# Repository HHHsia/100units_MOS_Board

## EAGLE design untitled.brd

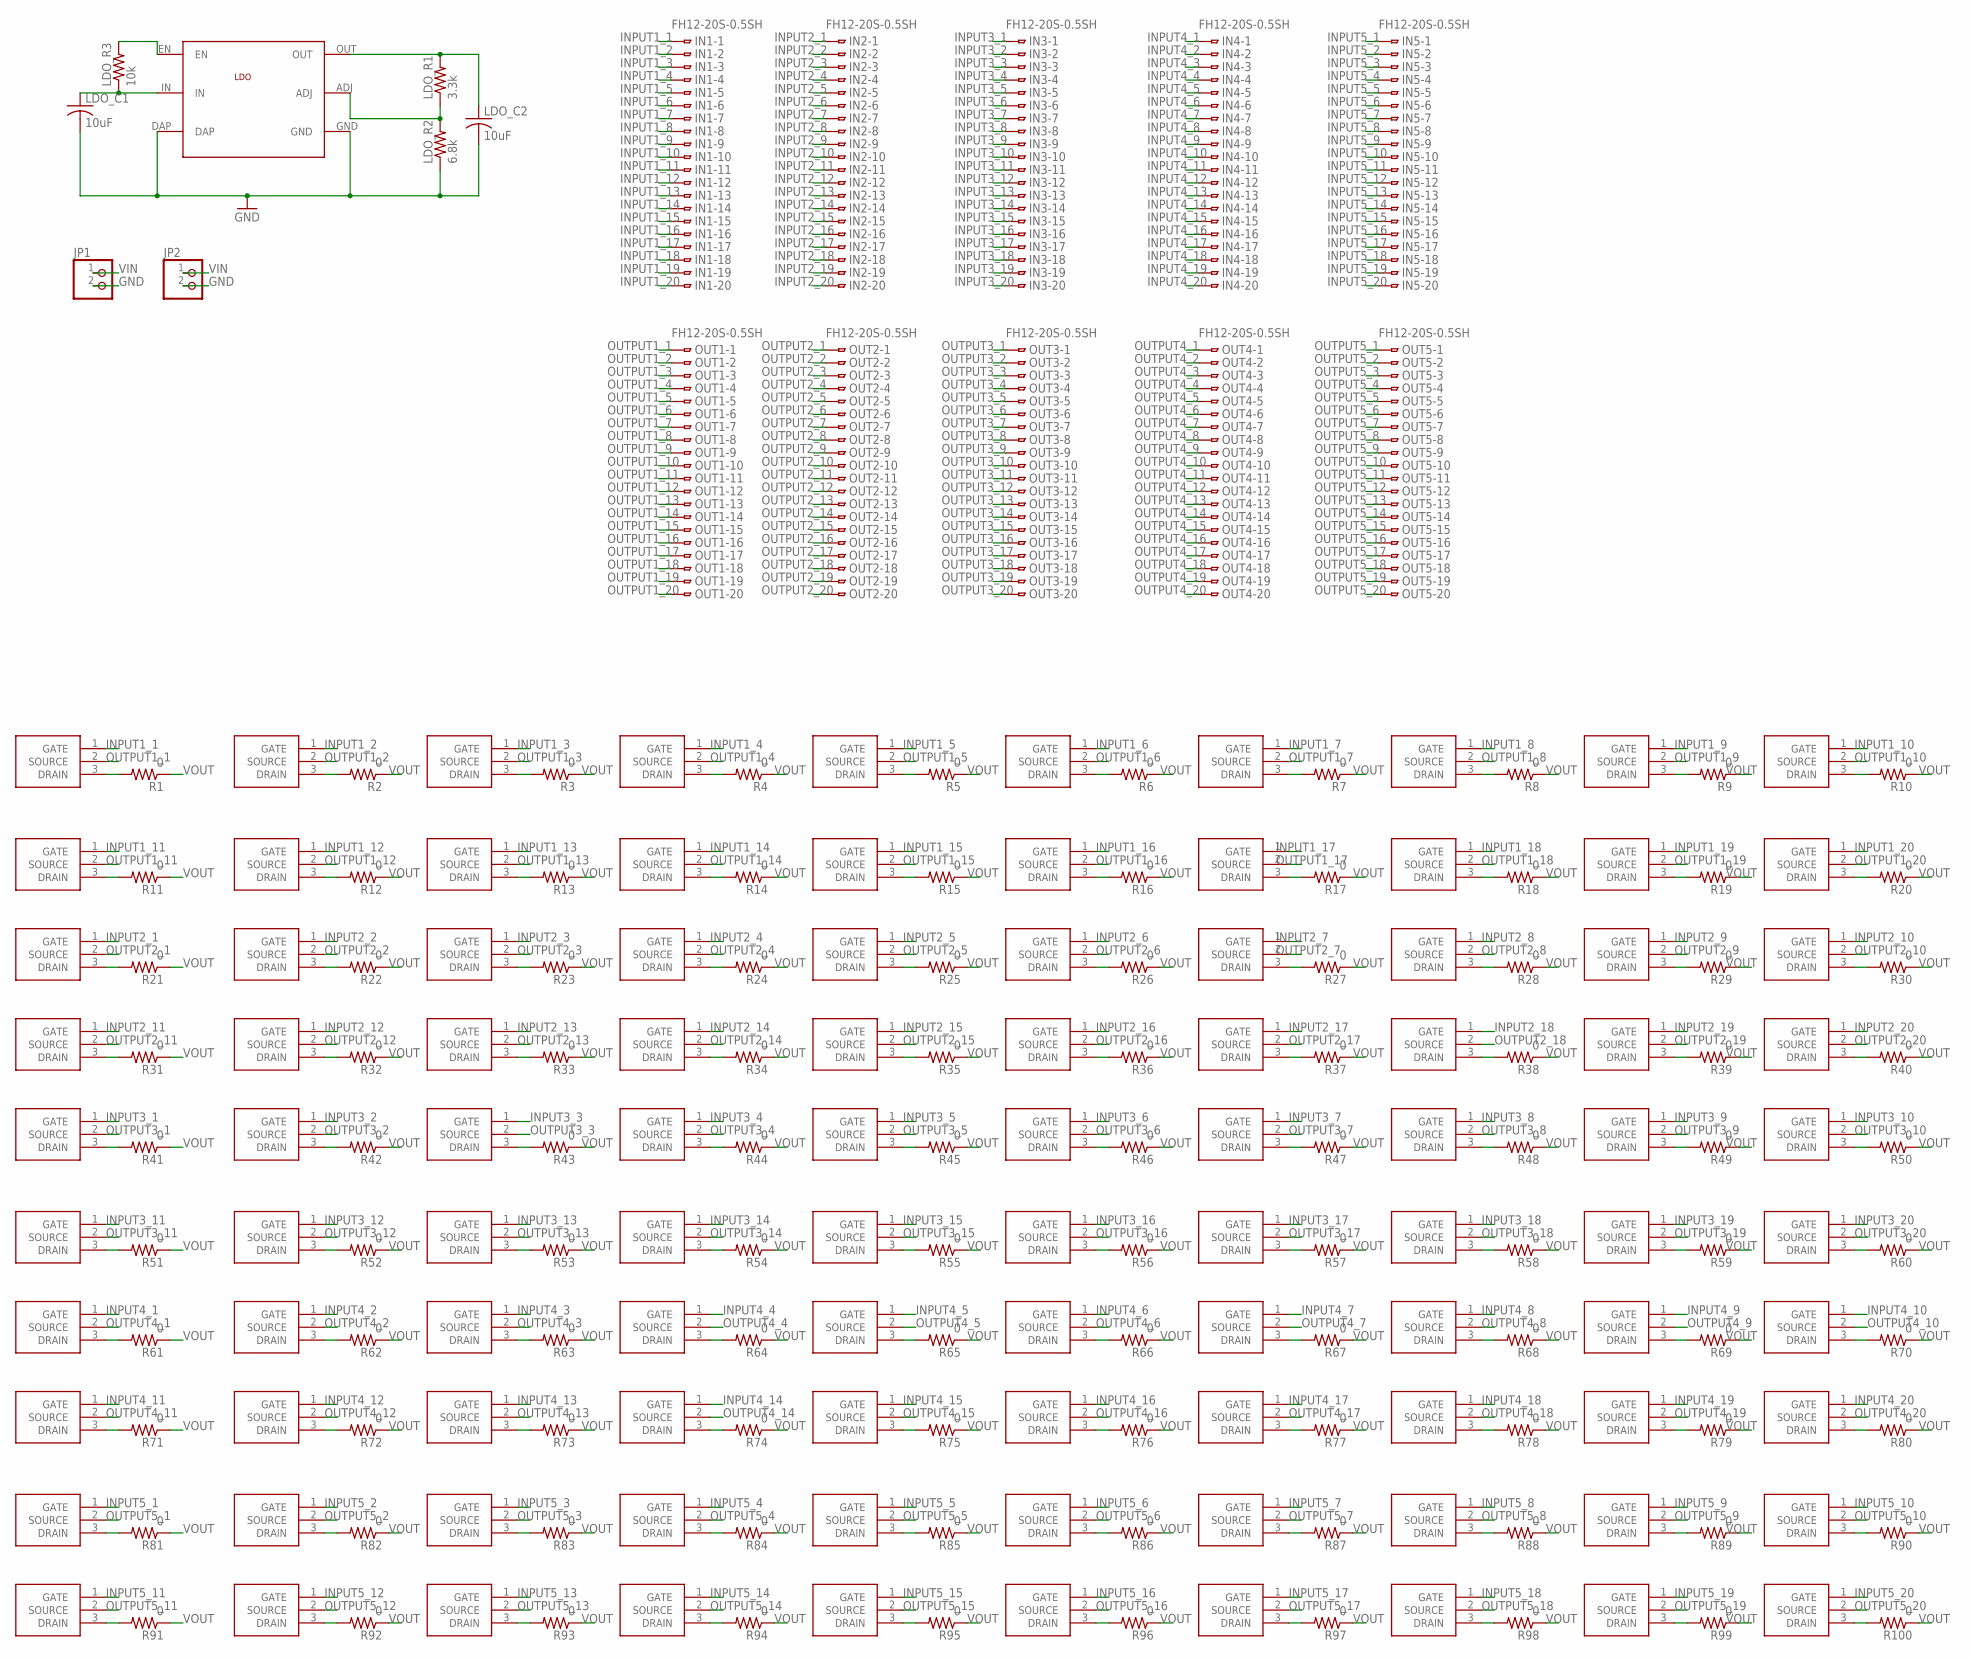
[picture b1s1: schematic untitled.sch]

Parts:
IN1, IN2, IN3, IN4, IN5: FH12-20S-0.5SH
JP1, JP2: PINHD-1X2; 1X02
LDO: LP38501TS_ADJ
LDO_C1, LDO_C2: 10uF; C0805
LDO_R1: 3.3k; R0805
LDO_R2: 6.8k; R0805
LDO_R3: 10k; R0805
MOS1, MOS2, MOS3, MOS4, MOS5, MOS6, MOS7, MOS8, MOS9, MOS10, MOS11, MOS12, MOS13, MOS14, MOS15, MOS16, MOS17, MOS18, MOS19, MOS20, MOS21, MOS22, MOS23, MOS24, MOS25, MOS26, MOS27, MOS28, MOS29, MOS30, MOS31, MOS32, MOS33, MOS34, MOS35, MOS36, MOS37, MOS38, MOS39, MOS40, MOS41, MOS42, MOS43, MOS44, MOS45, MOS46, MOS47, MOS48, MOS49, MOS50, MOS51, MOS52, MOS53, MOS54, MOS55, MOS56, MOS57, MOS58, MOS59, MOS60, MOS61, MOS62, MOS63, MOS64, MOS65, MOS66, MOS67, MOS68, MOS69, MOS70, MOS71, MOS72, MOS73, MOS74, MOS75, MOS76, MOS77, MOS78, MOS79, MOS80, MOS81, MOS82, MOS83, MOS84, MOS85, MOS86, MOS87, MOS88, MOS89, MOS90, MOS91, MOS92, MOS93, MOS94, MOS95, MOS96, MOS97, MOS98, MOS99, MOS100: NX6008NBKNX6008NBK; SOT95P240X110-3N
OUT1, OUT2, OUT3, OUT4, OUT5: FH12-20S-0.5SH
R1, R2, R3, R4, R5, R6, R7, R8, R9, R10, R11, R12, R13, R14, R15, R16, R17, R18, R19, R20, R21, R22, R23, R24, R25, R26, R27, R28, R29, R30, R31, R32, R33, R34, R35, R36, R37, R38, R39, R40, R41, R42, R43, R44, R45, R46, R47, R48, R49, R50, R51, R52, R53, R54, R55, R56, R57, R58, R59, R60, R61, R62, R63, R64, R65, R66, R67, R68, R69, R70, R71, R72, R73, R74, R75, R76, R77, R78, R79, R80, R81, R82, R83, R84, R85, R86, R87, R88, R89, R90, R91, R92, R93, R94, R95, R96, R97, R98, R99, R100: 0; R0805

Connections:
GND: JP1.2, JP2.2, LDO.DAP, LDO.GND, LDO_C1.2, LDO_C2.2, LDO_R2.1
INPUT1_1: IN1.1, MOS1.1 (GATE)
INPUT1_2: IN1.2, MOS2.1 (GATE)
INPUT1_3: IN1.3, MOS3.1 (GATE)
INPUT1_4: IN1.4, MOS4.1 (GATE)
INPUT1_5: IN1.5, MOS5.1 (GATE)
INPUT1_6: IN1.6, MOS6.1 (GATE)
INPUT1_7: IN1.7, MOS7.1 (GATE)
INPUT1_8: IN1.8, MOS8.1 (GATE)
INPUT1_9: IN1.9, MOS9.1 (GATE)
INPUT1_10: IN1.10, MOS10.1 (GATE)
INPUT1_11: IN1.11, MOS11.1 (GATE)
INPUT1_12: IN1.12, MOS12.1 (GATE)
INPUT1_13: IN1.13, MOS13.1 (GATE)
INPUT1_14: IN1.14, MOS14.1 (GATE)
INPUT1_15: IN1.15, MOS15.1 (GATE)
INPUT1_16: IN1.16, MOS16.1 (GATE)
INPUT1_17: IN1.17, MOS17.1 (GATE)
INPUT1_18: IN1.18, MOS18.1 (GATE)
INPUT1_19: IN1.19, MOS19.1 (GATE)
INPUT1_20: IN1.20, MOS20.1 (GATE)
INPUT2_1: IN2.1, MOS21.1 (GATE)
INPUT2_2: IN2.2, MOS22.1 (GATE)
INPUT2_3: IN2.3, MOS23.1 (GATE)
INPUT2_4: IN2.4, MOS24.1 (GATE)
INPUT2_5: IN2.5, MOS25.1 (GATE)
INPUT2_6: IN2.6, MOS26.1 (GATE)
INPUT2_7: IN2.7, MOS27.1 (GATE)
INPUT2_8: IN2.8, MOS28.1 (GATE)
INPUT2_9: IN2.9, MOS29.1 (GATE)
INPUT2_10: IN2.10, MOS30.1 (GATE)
INPUT2_11: IN2.11, MOS31.1 (GATE)
INPUT2_12: IN2.12, MOS32.1 (GATE)
INPUT2_13: IN2.13, MOS33.1 (GATE)
INPUT2_14: IN2.14, MOS34.1 (GATE)
INPUT2_15: IN2.15, MOS35.1 (GATE)
INPUT2_16: IN2.16, MOS36.1 (GATE)
INPUT2_17: IN2.17, MOS37.1 (GATE)
INPUT2_18: IN2.18, MOS38.1 (GATE)
INPUT2_19: IN2.19, MOS39.1 (GATE)
INPUT2_20: IN2.20, MOS40.1 (GATE)
INPUT3_1: IN3.1, MOS41.1 (GATE)
INPUT3_2: IN3.2, MOS42.1 (GATE)
INPUT3_3: IN3.3, MOS43.1 (GATE)
INPUT3_4: IN3.4, MOS44.1 (GATE)
INPUT3_5: IN3.5, MOS45.1 (GATE)
INPUT3_6: IN3.6, MOS46.1 (GATE)
INPUT3_7: IN3.7, MOS47.1 (GATE)
INPUT3_8: IN3.8, MOS48.1 (GATE)
INPUT3_9: IN3.9, MOS49.1 (GATE)
INPUT3_10: IN3.10, MOS50.1 (GATE)
INPUT3_11: IN3.11, MOS51.1 (GATE)
INPUT3_12: IN3.12, MOS52.1 (GATE)
INPUT3_13: IN3.13, MOS53.1 (GATE)
INPUT3_14: IN3.14, MOS54.1 (GATE)
INPUT3_15: IN3.15, MOS55.1 (GATE)
INPUT3_16: IN3.16, MOS56.1 (GATE)
INPUT3_17: IN3.17, MOS57.1 (GATE)
INPUT3_18: IN3.18, MOS58.1 (GATE)
INPUT3_19: IN3.19, MOS59.1 (GATE)
INPUT3_20: IN3.20, MOS60.1 (GATE)
INPUT4_1: IN4.1, MOS61.1 (GATE)
INPUT4_2: IN4.2, MOS62.1 (GATE)
INPUT4_3: IN4.3, MOS63.1 (GATE)
INPUT4_4: IN4.4, MOS64.1 (GATE)
INPUT4_5: IN4.5, MOS65.1 (GATE)
INPUT4_6: IN4.6, MOS66.1 (GATE)
INPUT4_7: IN4.7, MOS67.1 (GATE)
INPUT4_8: IN4.8, MOS68.1 (GATE)
INPUT4_9: IN4.9, MOS69.1 (GATE)
INPUT4_10: IN4.10, MOS70.1 (GATE)
INPUT4_11: IN4.11, MOS71.1 (GATE)
INPUT4_12: IN4.12, MOS72.1 (GATE)
INPUT4_13: IN4.13, MOS73.1 (GATE)
INPUT4_14: IN4.14, MOS74.1 (GATE)
INPUT4_15: IN4.15, MOS75.1 (GATE)
INPUT4_16: IN4.16, MOS76.1 (GATE)
INPUT4_17: IN4.17, MOS77.1 (GATE)
INPUT4_18: IN4.18, MOS78.1 (GATE)
INPUT4_19: IN4.19, MOS79.1 (GATE)
INPUT4_20: IN4.20, MOS80.1 (GATE)
INPUT5_1: IN5.1, MOS81.1 (GATE)
INPUT5_2: IN5.2, MOS82.1 (GATE)
INPUT5_3: IN5.3, MOS83.1 (GATE)
INPUT5_4: IN5.4, MOS84.1 (GATE)
INPUT5_5: IN5.5, MOS85.1 (GATE)
INPUT5_6: IN5.6, MOS86.1 (GATE)
INPUT5_7: IN5.7, MOS87.1 (GATE)
INPUT5_8: IN5.8, MOS88.1 (GATE)
INPUT5_9: IN5.9, MOS89.1 (GATE)
INPUT5_10: IN5.10, MOS90.1 (GATE)
INPUT5_11: IN5.11, MOS91.1 (GATE)
INPUT5_12: IN5.12, MOS92.1 (GATE)
INPUT5_13: IN5.13, MOS93.1 (GATE)
INPUT5_14: IN5.14, MOS94.1 (GATE)
INPUT5_15: IN5.15, MOS95.1 (GATE)
INPUT5_16: IN5.16, MOS96.1 (GATE)
INPUT5_17: IN5.17, MOS97.1 (GATE)
INPUT5_18: IN5.18, MOS98.1 (GATE)
INPUT5_19: IN5.19, MOS99.1 (GATE)
INPUT5_20: IN5.20, MOS100.1 (GATE)
unnamed: LDO.EN, LDO_R3.2
unnamed: MOS77.3 (DRAIN), R77.2
unnamed: MOS81.3 (DRAIN), R81.2
unnamed: LDO.ADJ, LDO_R1.1, LDO_R2.2
unnamed: MOS1.3 (DRAIN), R1.2
unnamed: MOS2.3 (DRAIN), R2.2
unnamed: MOS82.3 (DRAIN), R82.2
unnamed: MOS83.3 (DRAIN), R83.2
unnamed: MOS84.3 (DRAIN), R84.2
unnamed: MOS3.3 (DRAIN), R3.2
unnamed: MOS85.3 (DRAIN), R85.2
unnamed: MOS86.3 (DRAIN), R86.2
unnamed: MOS87.3 (DRAIN), R87.2
unnamed: MOS4.3 (DRAIN), R4.2
unnamed: MOS88.3 (DRAIN), R88.2
unnamed: MOS89.3 (DRAIN), R89.2
unnamed: MOS90.3 (DRAIN), R90.2
unnamed: MOS5.3 (DRAIN), R5.2
unnamed: MOS91.3 (DRAIN), R91.2
unnamed: MOS92.3 (DRAIN), R92.2
unnamed: MOS93.3 (DRAIN), R93.2
unnamed: MOS6.3 (DRAIN), R6.2
unnamed: MOS94.3 (DRAIN), R94.2
unnamed: MOS95.3 (DRAIN), R95.2
unnamed: MOS96.3 (DRAIN), R96.2
unnamed: MOS7.3 (DRAIN), R7.2
unnamed: MOS98.3 (DRAIN), R98.2
unnamed: MOS99.3 (DRAIN), R99.2
unnamed: MOS100.3 (DRAIN), R100.2
unnamed: MOS8.3 (DRAIN), R8.2
unnamed: MOS97.3 (DRAIN), R97.2
unnamed: MOS9.3 (DRAIN), R9.2
unnamed: MOS10.3 (DRAIN), R10.2
unnamed: MOS11.3 (DRAIN), R11.2
unnamed: MOS12.3 (DRAIN), R12.2
unnamed: MOS13.3 (DRAIN), R13.2
unnamed: MOS14.3 (DRAIN), R14.2
unnamed: MOS15.3 (DRAIN), R15.2
unnamed: MOS16.3 (DRAIN), R16.2
unnamed: MOS17.3 (DRAIN), R17.2
unnamed: MOS18.3 (DRAIN), R18.2
unnamed: MOS19.3 (DRAIN), R19.2
unnamed: MOS20.3 (DRAIN), R20.2
unnamed: MOS21.3 (DRAIN), R21.2
unnamed: MOS22.3 (DRAIN), R22.2
unnamed: MOS23.3 (DRAIN), R23.2
unnamed: MOS24.3 (DRAIN), R24.2
unnamed: MOS25.3 (DRAIN), R25.2
unnamed: MOS26.3 (DRAIN), R26.2
unnamed: MOS27.3 (DRAIN), R27.2
unnamed: MOS28.3 (DRAIN), R28.2
unnamed: MOS29.3 (DRAIN), R29.2
unnamed: MOS30.3 (DRAIN), R30.2
unnamed: MOS31.3 (DRAIN), R31.2
unnamed: MOS32.3 (DRAIN), R32.2
unnamed: MOS33.3 (DRAIN), R33.2
unnamed: MOS34.3 (DRAIN), R34.2
unnamed: MOS35.3 (DRAIN), R35.2
unnamed: MOS36.3 (DRAIN), R36.2
unnamed: MOS37.3 (DRAIN), R37.2
unnamed: MOS38.3 (DRAIN), R38.2
unnamed: MOS39.3 (DRAIN), R39.2
unnamed: MOS40.3 (DRAIN), R40.2
unnamed: MOS41.3 (DRAIN), R41.2
unnamed: MOS42.3 (DRAIN), R42.2
unnamed: MOS43.3 (DRAIN), R43.2
unnamed: MOS44.3 (DRAIN), R44.2
unnamed: MOS45.3 (DRAIN), R45.2
unnamed: MOS46.3 (DRAIN), R46.2
unnamed: MOS47.3 (DRAIN), R47.2
unnamed: MOS48.3 (DRAIN), R48.2
unnamed: MOS49.3 (DRAIN), R49.2
unnamed: MOS50.3 (DRAIN), R50.2
unnamed: MOS51.3 (DRAIN), R51.2
unnamed: MOS52.3 (DRAIN), R52.2
unnamed: MOS53.3 (DRAIN), R53.2
unnamed: MOS54.3 (DRAIN), R54.2
unnamed: MOS55.3 (DRAIN), R55.2
unnamed: MOS56.3 (DRAIN), R56.2
unnamed: MOS57.3 (DRAIN), R57.2
unnamed: MOS58.3 (DRAIN), R58.2
unnamed: MOS59.3 (DRAIN), R59.2
unnamed: MOS60.3 (DRAIN), R60.2
unnamed: MOS61.3 (DRAIN), R61.2
unnamed: MOS62.3 (DRAIN), R62.2
unnamed: MOS63.3 (DRAIN), R63.2
unnamed: MOS64.3 (DRAIN), R64.2
unnamed: MOS65.3 (DRAIN), R65.2
unnamed: MOS66.3 (DRAIN), R66.2
unnamed: MOS67.3 (DRAIN), R67.2
unnamed: MOS68.3 (DRAIN), R68.2
unnamed: MOS69.3 (DRAIN), R69.2
unnamed: MOS70.3 (DRAIN), R70.2
unnamed: MOS71.3 (DRAIN), R71.2
unnamed: MOS72.3 (DRAIN), R72.2
unnamed: MOS73.3 (DRAIN), R73.2
unnamed: MOS74.3 (DRAIN), R74.2
unnamed: MOS75.3 (DRAIN), R75.2
unnamed: MOS76.3 (DRAIN), R76.2
unnamed: MOS78.3 (DRAIN), R78.2
unnamed: MOS79.3 (DRAIN), R79.2
unnamed: MOS80.3 (DRAIN), R80.2
OUTPUT1_1: MOS1.2 (SOURCE), OUT1.1
OUTPUT1_2: MOS2.2 (SOURCE), OUT1.2
OUTPUT1_3: MOS3.2 (SOURCE), OUT1.3
OUTPUT1_4: MOS4.2 (SOURCE), OUT1.4
OUTPUT1_5: MOS5.2 (SOURCE), OUT1.5
OUTPUT1_6: MOS6.2 (SOURCE), OUT1.6
OUTPUT1_7: MOS7.2 (SOURCE), OUT1.7
OUTPUT1_8: MOS8.2 (SOURCE), OUT1.8
OUTPUT1_9: MOS9.2 (SOURCE), OUT1.9
OUTPUT1_10: MOS10.2 (SOURCE), OUT1.10
OUTPUT1_11: MOS11.2 (SOURCE), OUT1.11
OUTPUT1_12: MOS12.2 (SOURCE), OUT1.12
OUTPUT1_13: MOS13.2 (SOURCE), OUT1.13
OUTPUT1_14: MOS14.2 (SOURCE), OUT1.14
OUTPUT1_15: MOS15.2 (SOURCE), OUT1.15
OUTPUT1_16: MOS16.2 (SOURCE), OUT1.16
OUTPUT1_17: MOS17.2 (SOURCE), OUT1.17
OUTPUT1_18: MOS18.2 (SOURCE), OUT1.18
OUTPUT1_19: MOS19.2 (SOURCE), OUT1.19
OUTPUT1_20: MOS20.2 (SOURCE), OUT1.20
OUTPUT2_1: MOS21.2 (SOURCE), OUT2.1
OUTPUT2_2: MOS22.2 (SOURCE), OUT2.2
OUTPUT2_3: MOS23.2 (SOURCE), OUT2.3
OUTPUT2_4: MOS24.2 (SOURCE), OUT2.4
OUTPUT2_5: MOS25.2 (SOURCE), OUT2.5
OUTPUT2_6: MOS26.2 (SOURCE), OUT2.6
OUTPUT2_7: MOS27.2 (SOURCE), OUT2.7
OUTPUT2_8: MOS28.2 (SOURCE), OUT2.8
OUTPUT2_9: MOS29.2 (SOURCE), OUT2.9
OUTPUT2_10: MOS30.2 (SOURCE), OUT2.10
OUTPUT2_11: MOS31.2 (SOURCE), OUT2.11
OUTPUT2_12: MOS32.2 (SOURCE), OUT2.12
OUTPUT2_13: MOS33.2 (SOURCE), OUT2.13
OUTPUT2_14: MOS34.2 (SOURCE), OUT2.14
OUTPUT2_15: MOS35.2 (SOURCE), OUT2.15
OUTPUT2_16: MOS36.2 (SOURCE), OUT2.16
OUTPUT2_17: MOS37.2 (SOURCE), OUT2.17
OUTPUT2_18: MOS38.2 (SOURCE), OUT2.18
OUTPUT2_19: MOS39.2 (SOURCE), OUT2.19
OUTPUT2_20: MOS40.2 (SOURCE), OUT2.20
OUTPUT3_1: MOS41.2 (SOURCE), OUT3.1
OUTPUT3_2: MOS42.2 (SOURCE), OUT3.2
OUTPUT3_3: MOS43.2 (SOURCE), OUT3.3
OUTPUT3_4: MOS44.2 (SOURCE), OUT3.4
OUTPUT3_5: MOS45.2 (SOURCE), OUT3.5
OUTPUT3_6: MOS46.2 (SOURCE), OUT3.6
OUTPUT3_7: MOS47.2 (SOURCE), OUT3.7
OUTPUT3_8: MOS48.2 (SOURCE), OUT3.8
OUTPUT3_9: MOS49.2 (SOURCE), OUT3.9
OUTPUT3_10: MOS50.2 (SOURCE), OUT3.10
OUTPUT3_11: MOS51.2 (SOURCE), OUT3.11
OUTPUT3_12: MOS52.2 (SOURCE), OUT3.12
OUTPUT3_13: MOS53.2 (SOURCE), OUT3.13
OUTPUT3_14: MOS54.2 (SOURCE), OUT3.14
OUTPUT3_15: MOS55.2 (SOURCE), OUT3.15
OUTPUT3_16: MOS56.2 (SOURCE), OUT3.16
OUTPUT3_17: MOS57.2 (SOURCE), OUT3.17
OUTPUT3_18: MOS58.2 (SOURCE), OUT3.18
OUTPUT3_19: MOS59.2 (SOURCE), OUT3.19
OUTPUT3_20: MOS60.2 (SOURCE), OUT3.20
OUTPUT4_1: MOS61.2 (SOURCE), OUT4.1
OUTPUT4_2: MOS62.2 (SOURCE), OUT4.2
OUTPUT4_3: MOS63.2 (SOURCE), OUT4.3
OUTPUT4_4: MOS64.2 (SOURCE), OUT4.4
OUTPUT4_5: MOS65.2 (SOURCE), OUT4.5
OUTPUT4_6: MOS66.2 (SOURCE), OUT4.6
OUTPUT4_7: MOS67.2 (SOURCE), OUT4.7
OUTPUT4_8: MOS68.2 (SOURCE), OUT4.8
OUTPUT4_9: MOS69.2 (SOURCE), OUT4.9
OUTPUT4_10: MOS70.2 (SOURCE), OUT4.10
OUTPUT4_11: MOS71.2 (SOURCE), OUT4.11
OUTPUT4_12: MOS72.2 (SOURCE), OUT4.12
OUTPUT4_13: MOS73.2 (SOURCE), OUT4.13
OUTPUT4_14: MOS74.2 (SOURCE), OUT4.14
OUTPUT4_15: MOS75.2 (SOURCE), OUT4.15
OUTPUT4_16: MOS76.2 (SOURCE), OUT4.16
OUTPUT4_17: MOS77.2 (SOURCE), OUT4.17
OUTPUT4_18: MOS78.2 (SOURCE), OUT4.18
OUTPUT4_19: MOS79.2 (SOURCE), OUT4.19
OUTPUT4_20: MOS80.2 (SOURCE), OUT4.20
OUTPUT5_1: MOS81.2 (SOURCE), OUT5.1
OUTPUT5_2: MOS82.2 (SOURCE), OUT5.2
OUTPUT5_3: MOS83.2 (SOURCE), OUT5.3
OUTPUT5_4: MOS84.2 (SOURCE), OUT5.4
OUTPUT5_5: MOS85.2 (SOURCE), OUT5.5
OUTPUT5_6: MOS86.2 (SOURCE), OUT5.6
OUTPUT5_7: MOS87.2 (SOURCE), OUT5.7
OUTPUT5_8: MOS88.2 (SOURCE), OUT5.8
OUTPUT5_9: MOS89.2 (SOURCE), OUT5.9
OUTPUT5_10: MOS90.2 (SOURCE), OUT5.10
OUTPUT5_11: MOS91.2 (SOURCE), OUT5.11
OUTPUT5_12: MOS92.2 (SOURCE), OUT5.12
OUTPUT5_13: MOS93.2 (SOURCE), OUT5.13
OUTPUT5_14: MOS94.2 (SOURCE), OUT5.14
OUTPUT5_15: MOS95.2 (SOURCE), OUT5.15
OUTPUT5_16: MOS96.2 (SOURCE), OUT5.16
OUTPUT5_17: MOS97.2 (SOURCE), OUT5.17
OUTPUT5_18: MOS98.2 (SOURCE), OUT5.18
OUTPUT5_19: MOS99.2 (SOURCE), OUT5.19
OUTPUT5_20: MOS100.2 (SOURCE), OUT5.20
VIN: JP1.1, JP2.1, LDO.IN, LDO_C1.1, LDO_R3.1
VOUT: LDO.OUT, LDO_C2.1, LDO_R1.2, R1.1, R2.1, R3.1, R4.1, R5.1, R6.1, R7.1, R8.1, R9.1, R10.1, R11.1, R12.1, R13.1, R14.1, R15.1, R16.1, R17.1, R18.1, R19.1, R20.1, R21.1, R22.1, R23.1, R24.1, R25.1, R26.1, R27.1, R28.1, R29.1, R30.1, R31.1, R32.1, R33.1, R34.1, R35.1, R36.1, R37.1, R38.1, R39.1, R40.1, R41.1, R42.1, R43.1, R44.1, R45.1, R46.1, R47.1, R48.1, R49.1, R50.1, R51.1, R52.1, R53.1, R54.1, R55.1, R56.1, R57.1, R58.1, R59.1, R60.1, R61.1, R62.1, R63.1, R64.1, R65.1, R66.1, R67.1, R68.1, R69.1, R70.1, R71.1, R72.1, R73.1, R74.1, R75.1, R76.1, R77.1, R78.1, R79.1, R80.1, R81.1, R82.1, R83.1, R84.1, R85.1, R86.1, R87.1, R88.1, R89.1, R90.1, R91.1, R92.1, R93.1, R94.1, R95.1, R96.1, R97.1, R98.1, R99.1, R100.1

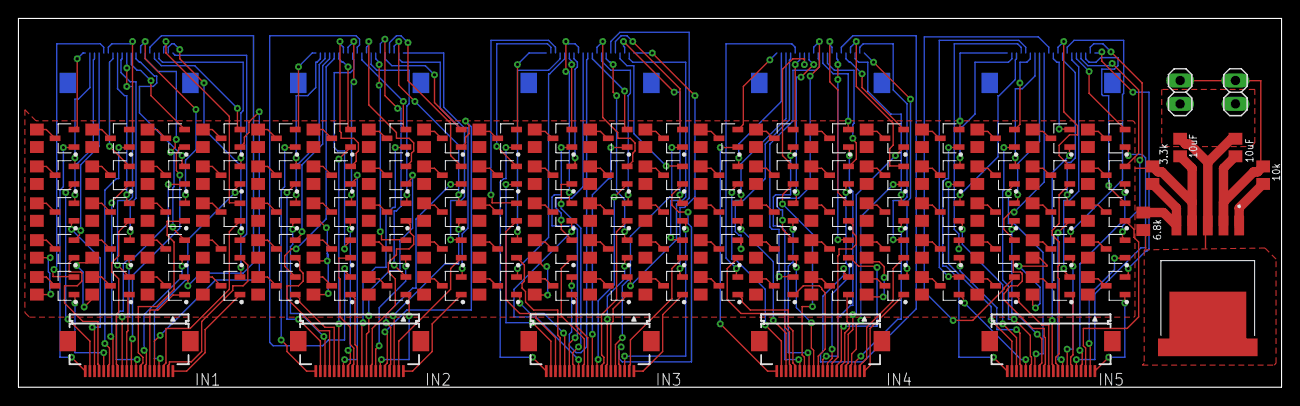
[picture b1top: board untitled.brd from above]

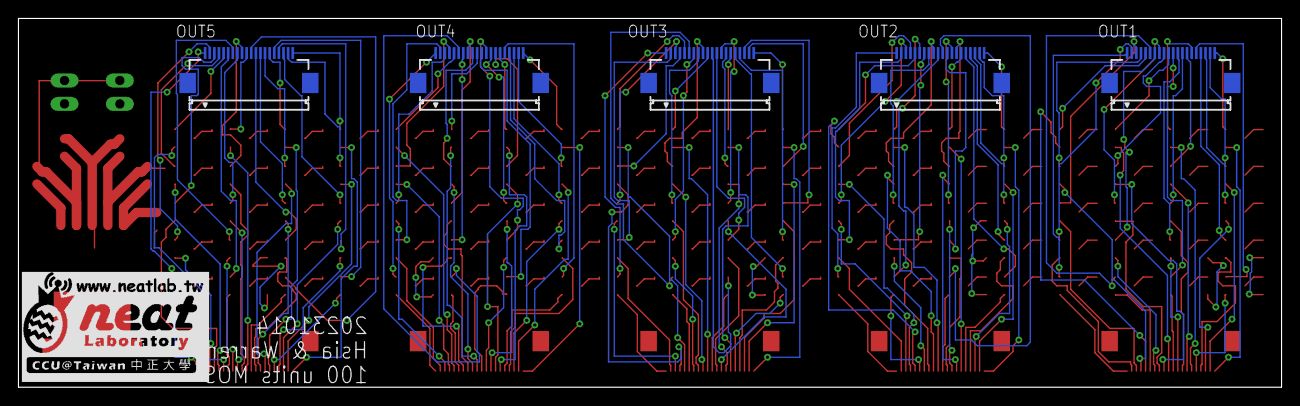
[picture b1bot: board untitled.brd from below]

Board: 2 copper layers, 137.0 x 40.0 mm, 219 parts (6 on the bottom side), 305 nets.

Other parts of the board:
U$1: LOGO_SCALE_2.0

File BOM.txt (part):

Partlist exported from C:/Users/PW0000/Downloads/100units_MOS_Board/untitled.sch at 2023/10/20 下午 04:18

Part   Value              Device             Package          Description                        MF MPN                OC_FARNELL OC_NEWARK POPULARITY SPICEPREFIX
IN1    FH12-20S-0.5SH     FH12-20S-0.5SH     FH12-20S-0.5SH   0.5mm Pitch Connectors For FPC/FFC    FH12-20S-0.5SH(55) 1324549    34M6166   0                     
IN2    FH12-20S-0.5SH     FH12-20S-0.5SH     FH12-20S-0.5SH   0.5mm Pitch Connectors For FPC/FFC    FH12-20S-0.5SH(55) 1324549    34M6166   0                     
IN3    FH12-20S-0.5SH     FH12-20S-0.5SH     FH12-20S-0.5SH   0.5mm Pitch Connectors For FPC/FFC    FH12-20S-0.5SH(55) 1324549    34M6166   0                     
IN4    FH12-20S-0.5SH     FH12-20S-0.5SH     FH12-20S-0.5SH   0.5mm Pitch Connectors For FPC/FFC    FH12-20S-0.5SH(55) 1324549    34M6166   0                     
IN5    FH12-20S-0.5SH     FH12-20S-0.5SH     FH12-20S-0.5SH   0.5mm Pitch Connectors For FPC/FFC    FH12-20S-0.5SH(55) 1324549    34M6166   0                     
JP1                       PINHD-1X2          1X02             PIN HEADER                                                                    98                    
JP2                       PINHD-1X2          1X02             PIN HEADER                                                                    98                    
LDO                       LP38501TS_ADJ      LP38501TS_ADJ                                                                                                        
LDO_C1 10uF               C-USC0805          C0805            CAPACITOR, American symbol                                                    63         C          
LDO_C2 10uF               C-USC0805          C0805            CAPACITOR, American symbol                                                    63         C          
LDO_R1 3.3k               R-US_R0805         R0805            RESISTOR, American symbol                                                     85         R          
LDO_R2 6.8k               R-US_R0805         R0805            RESISTOR, American symbol                                                     85         R          
LDO_R3 10k                R-US_R0805         R0805            RESISTOR, American symbol                                                     85         R          
MOS1   NX6008NBKNX6008NBK NX6008NBKNX6008NBK SOT95P240X110-3N                                                                                                     
MOS2   NX6008NBKNX6008NBK NX6008NBKNX6008NBK SOT95P240X110-3N                                                                                                     
MOS3   NX6008NBKNX6008NBK NX6008NBKNX6008NBK SOT95P240X110-3N                                                                                                     
MOS4   NX6008NBKNX6008NBK NX6008NBKNX6008NBK SOT95P240X110-3N                                                                                                     
MOS5   NX6008NBKNX6008NBK NX6008NBKNX6008NBK SOT95P240X110-3N                                                                                                     
MOS6   NX6008NBKNX6008NBK NX6008NBKNX6008NBK SOT95P240X110-3N                                                                                                     
MOS7   NX6008NBKNX6008NBK NX6008NBKNX6008NBK SOT95P240X110-3N                                                                                                     
MOS8   NX6008NBKNX6008NBK NX6008NBKNX6008NBK SOT95P240X110-3N                                                                                                     
MOS9   NX6008NBKNX6008NBK NX6008NBKNX6008NBK SOT95P240X110-3N                                                                                                     
MOS10  NX6008NBKNX6008NBK NX6008NBKNX6008NBK SOT95P240X110-3N                                                                                                     
MOS11  NX6008NBKNX6008NBK NX6008NBKNX6008NBK SOT95P240X110-3N                                                                                                     
MOS12  NX6008NBKNX6008NBK NX6008NBKNX6008NBK SOT95P240X110-3N                                                                                                     
MOS13  NX6008NBKNX6008NBK NX6008NBKNX6008NBK SOT95P240X110-3N                                                                                                     
MOS14  NX6008NBKNX6008NBK NX6008NBKNX6008NBK SOT95P240X110-3N                                                                                                     
MOS15  NX6008NBKNX6008NBK NX6008NBKNX6008NBK SOT95P240X110-3N                                                                                                     
MOS16  NX6008NBKNX6008NBK NX6008NBKNX6008NBK SOT95P240X110-3N                                                                                                     
MOS17  NX6008NBKNX6008NBK NX6008NBKNX6008NBK SOT95P240X110-3N                                                                                                     
MOS18  NX6008NBKNX6008NBK NX6008NBKNX6008NBK SOT95P240X110-3N                                                                                                     
MOS19  NX6008NBKNX6008NBK NX6008NBKNX6008NBK SOT95P240X110-3N                                                                                                     
MOS20  NX6008NBKNX6008NBK NX6008NBKNX6008NBK SOT95P240X110-3N                                                                                                     
MOS21  NX6008NBKNX6008NBK NX6008NBKNX6008NBK SOT95P240X110-3N                                                                                                     
MOS22  NX6008NBKNX6008NBK NX6008NBKNX6008NBK SOT95P240X110-3N                                                                                                     
MOS23  NX6008NBKNX6008NBK NX6008NBKNX6008NBK SOT95P240X110-3N                                                                                                     
MOS24  NX6008NBKNX6008NBK NX6008NBKNX6008NBK SOT95P240X110-3N                                                                                                     
MOS25  NX6008NBKNX6008NBK NX6008NBKNX6008NBK SOT95P240X110-3N                                                                                                     
MOS26  NX6008NBKNX6008NBK NX6008NBKNX6008NBK SOT95P240X110-3N                                                                                                     
MOS27  NX6008NBKNX6008NBK NX6008NBKNX6008NBK SOT95P240X110-3N                                                                                                     
MOS28  NX6008NBKNX6008NBK NX6008NBKNX6008NBK SOT95P240X110-3N                                                                                                     
MOS29  NX6008NBKNX6008NBK NX6008NBKNX6008NBK SOT95P240X110-3N                                                                                                     
MOS30  NX6008NBKNX6008NBK NX6008NBKNX6008NBK SOT95P240X110-3N                                                                                                     
MOS31  NX6008NBKNX6008NBK NX6008NBKNX6008NBK SOT95P240X110-3N                                                                                                     
MOS32  NX6008NBKNX6008NBK NX6008NBKNX6008NBK SOT95P240X110-3N                                                                                                     
MOS33  NX6008NBKNX6008NBK NX6008NBKNX6008NBK SOT95P240X110-3N                                                                                                     
MOS34  NX6008NBKNX6008NBK NX6008NBKNX6008NBK SOT95P240X110-3N                                                                                                     
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
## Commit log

2024-07-05 0705
